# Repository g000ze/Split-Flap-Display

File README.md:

## Intro
Older people (like me) look back with nostalgia at train stations and airports, middle-aged people are captivated by technology, and the younger generation is excited by the clattering sound combined with the non-virtual movement. The split flap display remains a fascinating display panel for text and small animations.

One day, while watching a video about split flap displays, I suddenly felt the desire to own one. After a relatively short research, I realized that only a few manufacturers build such displays. There are, for example, [Oat Foundry](https://www.oatfoundry.com/), [Vestaboard](https://www.vestaboard.com/), [Scott Bezek](https://github.com/scottbez1/splitflap) or the one called "Split Flap Display Manufacturer." No matter which manufacturer you choose, the displays are either very expensive or don't meet my requirements. So I decided to try building one myself.

A typical split flap display looks best when it can display text. This text is naturally composed of characters, i.e., letters, numbers, and special characters. Optionally, symbols, colors, or images can also be displayed. A character is represented on the display by a so-called module. A module consists of a housing, a stepper motor, a motor driver, a PCB that connects the driver and the motor, a carousel, 50 flaps for the characters, and, of course, various spacers and screws that hold the whole thing together. A magnetic sensor (Hall effect sensor) is also integrated into the carousel, which tells the microprocessor when position 0 or the home position has been reached.

As already mentioned, a single module produces little effect, so we want multiple modules for a display to achieve an intense visual effect. I decided to control eight modules with an [Arduino Micro](https://docs.arduino.cc/hardware/micro/). The modules therefore always come in units of eight. The Micro offers 20 digital input/output pins. Two of these are required per module: an output pin as a stepper for the driver and an input pin for the Hall effect sensor to determine the feedback for a full rotation of the carousel. This means a total of 16 Arduino pins are used for eight modules. The Arduino, in turn, is placed on the backplane PCB, where the modules are plugged into so-called card edge connectors. This PCB primarily controls two things:
- The digital communication between the Arduino and the modules (drivers & Hall sensors)
- The power supply for all electronics, including the motors

**Animation of spinning spool using OpenSCAD**

[![Spinning Carousel]](https://github.com/user-attachments/assets/b8cbd226-f410-4f9d-896a-09aa130f1321)

[![Exploded View]](https://github.com/user-attachments/assets/ecffe0bf-9c8d-47f0-b8ce-c02ede4a916f)

## The Housing
The housing is used to position the motor, along with the carousel and flaps, as well as the PCB with the Hall sensor. If everything is exactly right, the flaps will drop at the right time and the magnet will move correctly over the sensor. I used 0.8 mm sheet steel for the housing. The 3D OpenSCAD drawing can be found [here](https://github.com/g000ze/Split-Flap-Display/blob/main/OpenSCAD/Chassis.scad). I found a company in Switzerland called [Blexon](https://blexon.com), that will punch and bend the housing according to my specifications.

## The Stepper Motor
Normally, Nema 17 stepper motors are mounted on the side where the shaft is located. This display is different; the motor must be mounted on one side, and the shaft, where the carousel is screwed to, must be on the opposite side. The [17HS13-0404D](https://www.omc-stepperonline.com/de/doppel-schacht-nema-17-bipolar-1-8deg-26ncm-36-8oz-in-0-4a-12v-42x34mm-4-draehte-17hs13-0404d) is the only Nema 17 I could find with the shaft on the opposite side from where it is mounted. This motor is actually a "dual shaft" motor. The 17HS13-0404D is powered by +12 volts.

## The Driver
To operate a stepper motor, you need a driver. There are many. I experimented with stepper motor drivers for a long time until I finally came across the [TMC2208](https://www.digikey.ch/de/products/detail/watterott-electronic-gmbh/20170003-002/10071142) "Silent Step Stick" from [Watterott](https://learn.watterott.com/de/silentstepstick/). This driver allows the 17HS13-0404D to run almost silently. Finally, the sound of a split-flap display plays a crucial role. We want to hear only the flaps clattering, not the motors.

## The PCBs
Two different types of PCBs are required. One is a small PCB that is attached to each module. It essentially carries the driver and the Hall sensor. The other is the backplane PCB, which connects the Arduino's electronic wires to the eight modules via card-edge connectors. The six connections that run via the card-edge connectors are:
- Hall sensor
- GND
- +5V
- Step
- GND
- +12V

The TMC2208 and the Hall sensor on the module PCB each operate at +5 VCC, while the motor naturally requires 12 volts.

## The Carousel
The Carousel is attached to the pouley on the motor shaft so that it can be rotated by the steppermotor. It also holds the 50 flaps in position. The stepper motor is located inside the carousel. With its 82mm diameter, the carousel fits perfectly around the motor and there's enough space for the 50 flap positions. The two wheels are different, as the left wheel contains spokes, while the right wheel is open.

I decided to use [3mm PVC plates](https://www.vink.ch/wa_files/Produktblatt_20PVC-U_20TROVIDUR_20EC_205_3_2015_20Ind.pdf) for the carousel. A company named [Waterjet](https://www.waterjet.ch/) located in Switzerland did the water cutting to cut out the carousel wheels.

## The Pouley
The pouley connects the motor and the carousel together. [This](https://www.pololu.com/product/1998) one was actually the only one I found to suit the motor shaft. So I bought it, even though it is insanely overpriced.

## The Flaps
The flaps are the essential parts, since they show the text that you want to see. Basically almost all kind of fonts, characters, signs and pictures are possible. After endless searching, trying and disapointments, I found a company named [Ren Peck](http://www.ren-peck.com/) in China who was willing to create what I am looking for. In fact it is the very same company that created the flaps for [Scott Bezek](https://github.com/scottbez1/splitflap)s Split Flap Display. 

One flap has basically the size of 40mm height and 50mm width. There are two little notches on each side in order to hold them in the carousel and to make them actually flip down. 

## The Software
The software was mainly written by me. See GitHub repository for details and ask me if you get any questions or suggestions regarding that.

## Other

## Tools Used
- OpenSCAD: https://openscad.org/
- KiCad: https://www.kicad.org/
- FreeCAD: https://www.freecad.org/
- For the Raspberry Pi to communicate with Arduino using I2C, I used this extension: https://github.com/tasoftch/php-i2c-extension

## Parts
### Module

| Part                              | Nr. | Provider            | Model           | Link                                                                                                                               |
|-----------------------------------|-----|---------------------|-----------------|------------------------------------------------------------------------------------------------------------------------------------|
| Housing                           | 1   | Blexon Galgenen     |                 | https://blexon.com/                                                                                                                |
| Stepper Motor                     | 2   | Stepper Online      | 17HS13-0404D    | https://www.omc-stepperonline.com/de/doppel-schacht-nema-17-bipolar-1-8deg-26ncm-36-8oz-in-0-4a-12v-42x34mm-4-draehte-17hs13-0404d |
| Wheels for the Carousel           | 3   | Waterjet Mörschwil  |                 | https://www.waterjet.ch/                                                                                                           |
| Flaps                             | 4   | Ren Peck China      |                 | https://www.alibaba.com/product-detail/China-Ren-peck-supply-emotion-cards-60650877066.html                                        |
| Pouley 5mm Shaft, M3 Holes        | 5   | Eckstein            |                 | https://eckstein-shop.de/PololuUniversalAluminumMountingHubfor5mmShaft2CM3Holes2-Pack or https://www.pololu.com/product/1998       |
| PCB                               | 6   | JLCPCB              |                 | https://jlcpcb.com/                                                                                                                |
| Stepper Driver                    | 7   | Digikey             | TMC2208         | https://www.digikey.ch/de/products/detail/analog-devices-inc-maxim-integrated/TMC2208SILENTSTEPSTICK/6873626                       |
| Spacer Motor 20mm                 | 8   | Axxatronic          | OG-PA-6-3,2-20  | https://www.axxatronic.de/distanzhuelsen/kunststoff/OG-PA-0060-0032.html                                                           |
| Spacer Carousel 51mm              | 8   | Axxatronic          | OG-PA-6-3,2-51  | https://www.axxatronic.de/distanzhuelsen/kunststoff/OG-PA-0060-0032.html                                                           |
| Spacer PCB 2mm                    | 8   | Axxatronic          | OG-PA-6-3,2-02  | https://www.axxatronic.de/distanzhuelsen/kunststoff/OG-PA-0060-0032.html                                                           |
| Magnet                            | 9   | supermagnete.ch     | S-02-02-N       | https://www.supermagnete.ch/scheibenmagnete-neodym/scheibenmagnet-2mm-2mm_S-02-02-N                                                |
| Screws                            | 10  | Schraubenking       |                 | https://www.schraubenking.ch/                                                                                                      |

### Module PCB 

| Part                              | Nr. | Provider            | Model           | Link                                                                                                                               |
|-----------------------------------|-----|---------------------|-----------------|------------------------------------------------------------------------------------------------------------------------------------|
| 10K Resistor                      | 1   | Digikey             | CRGCQ1210F10K   | https://www.digikey.ch/en/products/detail/te-connectivity-passive-product/CRGCQ1210F10K/8576485                                    |
| Header Connector                  | 2   | Digikey             | NPPC082KFMS-RC  | https://www.digikey.ch/en/products/detail/sullins-connector-solutions/NPPC082KFMS-RC/776176                                        |
| Hall Sensor                       | 3   | Digikey             | 620-1002-1-ND   | https://www.digikey.ch/de/products/detail/allegro-microsystems/A1102LLHLT-T/1006577                                                |
| 47 µF Capacitor                   | 4   | Digikey             | APA0606470M025R | https://www.digikey.ch/en/products/detail/kyocera-avx/APA0606470M025R/15195370                                                     |
| Wires Connector                   | 5   | Digikey             | 009176004873906 | https://www.digikey.ch/en/products/detail/kyocera-avx/009176004873906/8540378                                                      |

### Backplane PCB 

| Part                              | Nr. | Provider            | Model           | Link                                                                                                                               |
|-----------------------------------|-----|---------------------|-----------------|------------------------------------------------------------------------------------------------------------------------------------|
| Arduino Micro                     | 1   | Digikey             | A000053         | https://www.digikey.ch/de/products/detail/arduino/A000053/4486332                                                                  |
| Voltage Converter                 | 2   | Digikey             | R-78K5.0-1.0    | https://www.digikey.ch/en/products/detail/recom-power/R-78K5-0-1-0/18093047                                                        |
| Card Edge Connector (old version) | 3   | Digikey             | EDC305122-ND    | https://www.digikey.ch/de/products/detail/edac-inc/305-012-520-202/107502                                                          |
| Card Edge Connector (new version) | 3   | Digikey             | EBC06DRXH       | https://www.digikey.ch/de/products/detail/sullins-connector-solutions/EBC06DRXH/927248                                             |
| Connector Header for Arduino      | 4   | Digikey             | 1-215307-7      | https://www.digikey.ch/en/products/detail/te-connectivity-amp-connectors/1-215307-7/2278494                                        |
| Screw Terminal for 12V Power      | 5   | Digikey             | 282836-1        | https://www.digikey.ch/en/products/detail/te-connectivity-amp-connectors/282836-1/2222325                                          |

Generated by https://www.tablesgenerator.com/markdown_tables

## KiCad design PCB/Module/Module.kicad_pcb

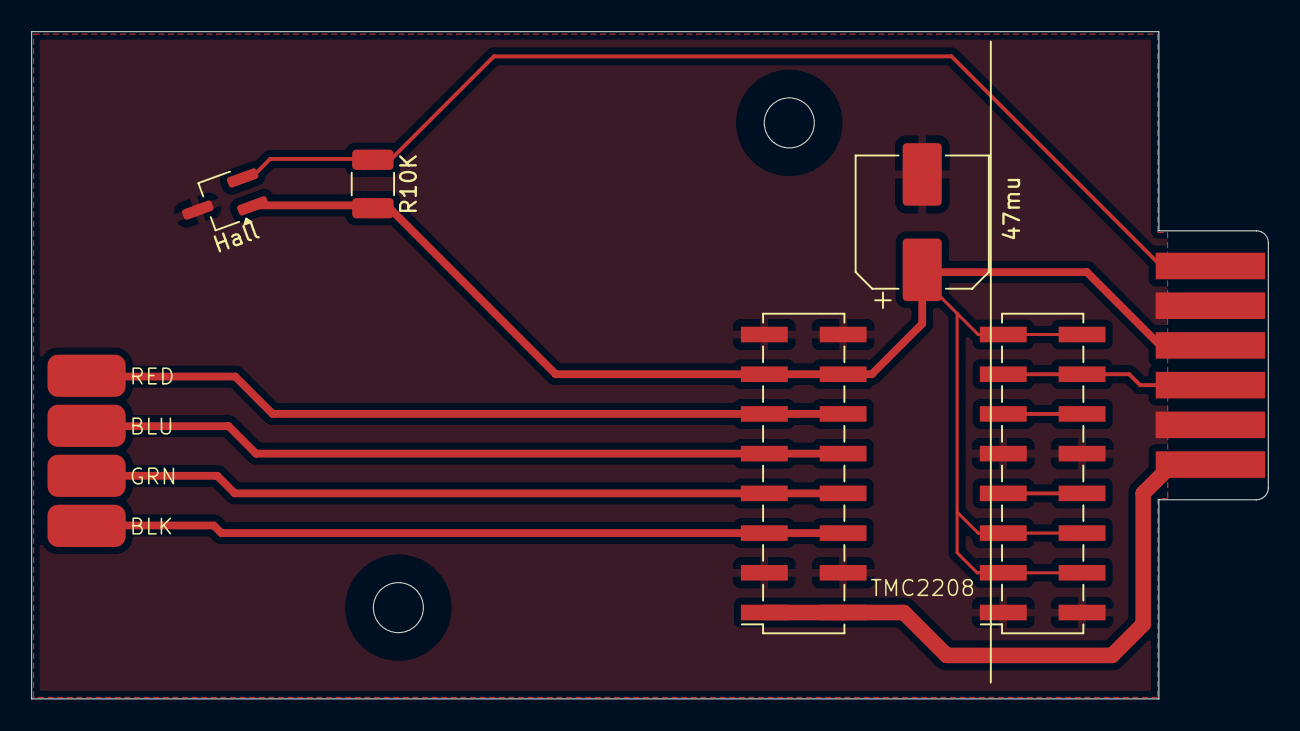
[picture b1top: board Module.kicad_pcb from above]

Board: 2 copper layers, 79.1 x 42.7 mm, 5 parts (0 on the bottom side), 11 nets.

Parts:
47mu: CP_Elec_8x5.4
 : PinSocket_2x08_P2.54mm_Vertical_SMD
 #2: PinSocket_2x08_P2.54mm_Vertical_SMD
Hall: SOT-23W_Handsoldering
R10K: R_1210_3225Metric_Pad1.30x2.65mm_HandSolder

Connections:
+5V: 47mu.1, .13, .14, #2.3 MS1, #2.4 MS1, #2.5 MS2, #2.6 MS2, #2.15 Dir, #2.16 Dir, Hall.1, R10K.2
+12V: .1, .2
A1: .9, .10
A2: .11, .12
B1: .7, .8
B2: .5, .6
Clock: #2.11, #2.12
GND: 47mu.2, .3, .4, .15, .16, #2.1 Enable, #2.2 Enable, #2.9 PDN, #2.10 PDN, Hall.3
Hall: Hall.2, R10K.1
NC: #2.7, #2.8
Step: #2.13, #2.14

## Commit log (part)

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2023-01-21 test
2023-01-22 remove my very first test file...
2023-01-22 add PHP code and library, that communicates with arduino.
2023-01-22 Add arduino code and create separate directories.
2024-09-28 added OpenSCAD files with animated module
2024-10-08 make spinning carousel faster
2024-10-11 small changes in code
2024-10-12 Update README.md
    add video
2024-10-12 Update README.md
    remove video
2024-11-06 new version with spinning carousel and optimized code
2024-11-06 add license text
2024-11-07 add _font_setup.scad and _settings.scad
2024-11-07 correct counter in 3D rotating_carousel module and move settings.scad to _settings.scad
2024-11-15 Update README.md, added new animated GIF
2024-11-15 Update README.md with better animated GIF
    better animated GIF with spinning carousel and printed flaps
2024-11-15 added start_row and end_row support. Little code cleanup.
2024-11-15 add render() to PVC picture for better preview performance
2024-11-15 Replace MS-Gothic with better font
2024-11-22 Cut off blind only for backside flaps
2024-11-22 modify module flap_with_char and add module draw_half_letter
2024-11-22 count by rows and cols instead of cols and rows. Small difference, big impact.
2024-11-22 add support for printing squares and colors
2024-11-24 fix wrong translate in rotating_carousel module of 3D library
2024-11-29 Update README.md
    Add mp4 video
2024-11-29 remove MS Gothic font from _font_setup.scad
2024-12-01 small code style adjustments
2024-12-01 Code optimization and beautifying
2024-12-02 small corrections for settings, remove obsolete font
2024-12-05 add example_flaps_bolt to Split_Flap_Module.scad
2024-12-05 new settings for PCB
2024-12-05 new code for PCB and adjust code for motor position
2024-12-06 add KiCad PCB files
2024-12-22 Update README.md
    Add YouTube link
2024-12-22 Update README.md with YouTube link
2024-12-22 Update README.md
    Fix link in README.md
2024-12-31 better update_ms_pos support and other improvements
2025-01-01 fix error in Split_Flap.ino and simplify code in inputs.ino
2025-02-25 code cleanup and adjustments
2025-04-13 small code changes
2025-05-04 add exploded view of Split Flap Module
2025-05-04 add index.html
2025-05-04 trying to embed video
2025-05-04 remove docs directory
2025-05-10 get rid of confusing side effects when drawing flaps with half letters
2025-05-22 new PHP library, supporting multiple arduinos
2025-06-02 brand new version of PHP library
2025-06-02 add html example files
2025-06-02 small cosmetical change to text.php
2025-06-02 adjust style information in index.php
2025-06-15 fill up posted string with spaces
2025-06-15 small changes to web design
2025-06-28 add spacers between housing and pcb
2025-06-28 add the 'wipe to the end' function
2025-07-08 update module PCB with 3D wires connector
2025-07-08 rename module PCB files from SplitFlap.kicad to Module.kicad
2025-07-08 update backplane PCB
2025-07-09 add missing pins_v2.ino
2025-07-23 set PDN pin on stepper driver to GND
2025-08-16 update backplane PCB with I2C connectors and new 3D models
2025-08-23 add virtual bolt to show better flaps behaviour in OpenSCAD animation
2025-08-23 code cleanup. move colors from library to Split_Flap_Module.scad. Remove unneeded modules and snippets.
2025-08-23 separate module chassis_bolt to chassis_bolt_screw and chassis_bolt_nut
2025-08-24 remove unneeded fn variables. Simplify code. Add faster version of karussell_scheibe with linear_extrude.
2025-08-25 add simpler module for carousel library
2025-08-25 add description
2025-08-25 add new settings for new carousel module. Also add more description. Reduce letter_facet_number for faster rendering.
2025-08-31 add right and left parallel start timing
2025-08-31 fix small failure where the hole for the axis gets executet four times instead of one time
2025-08-31 correct CSS and add description for changeing rows and cols.
2025-09-08 fix small issue with left animation
2025-09-26 rename array from chars to characters
2025-09-26 remove old code, rename array from chars to characters, simplify code with ternary operators
2025-09-26 remove empty line
2025-09-26 replace white flap with '/' character instead of 'w'.
2025-09-26 correct px padding with em
2025-10-05 remove translate if explode > 0
2025-10-05 remove 'check' module. Correct 'flap_with_char' module, so that the last flaps display correctly. Give 'example_flap_bottom' module the possibility to display any flap.
2025-10-05 add fully colored flaps example
2025-10-05 extend from 32 to 48 modules
2025-10-05 rename animation from 'right' to 'right_snake' and 'right_par' to 'right'. Same for 'left...'. Add another row of 16 modules.
2025-11-17 code cleanup and additional animation features
2025-11-29 code cleanup and better receive_i2c_event function.
2025-11-29 remove unneeded delay in motor_run function
2025-12-23 update PCB to newest version, remove obsolete files
2025-12-23 add slowdown function and code cleanup
2026-01-18 Update component list and adjust numbering
2026-01-18 Replace PCB images in README
    Updated images for Module PCB and Backplane PCB sections.
2026-01-18 Remove PCB images from README
    Removed two images related to the PCB module and backplane from the README.
2026-02-13 remove color-modes.js in index.php to enable dark mode
2026-05-14 correct return value for spinning modules
2026-05-14 revert back last change, return 255 for spinning modules
2026-06-09 add pin headers on PCB. fix white shadow on flap spool.
2026-06-17 Update README.md to fix image links
    Removed outdated link and fixed image link for spinning carousel.
2026-06-17 Correct image link for spinning carousel
    Fix image link formatting for spinning carousel in README.
